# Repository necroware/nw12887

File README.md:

# Necroware's NW12887 RTC module

__ATTENTION:__ *this project was made for the SSOP-24 version of the RTC IC, if
you need the SO-24 version go for https://github.com/necroware/nwX287 project
instead*

This is a drop-in replacement for RTC modules with solid body. Such modules were
widely used on 486 and Pentium mainboards back in the days. After so many years
the battery inside of such modules got empty and there is no way to exchange it.
With empty battery BIOS settings can not be saved and so many mainboards can't
even boot properly. This alternative solution has a socket for CR1225 and the
battery can be easily replaced again, when it gets empty.

This part should be compatible with following RTC modules:

* Dallas DS1287 / DS12887 / DS12B887
* Benchmarq BQ3287
* ODIN OEC12C887

## Bill of Materials

Part | # | Description
-----|---|-------------------------------------
U1   | 1 | Real-Time Clock BQ3285LDSS SSOP-24
Y1   | 1 | Crystal oscillator 32.768kHz 6pF
BT1  | 1 | CR1220 / CR1225 SMD battery holder

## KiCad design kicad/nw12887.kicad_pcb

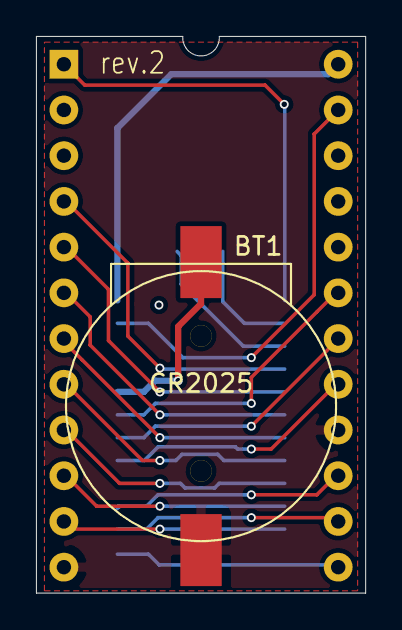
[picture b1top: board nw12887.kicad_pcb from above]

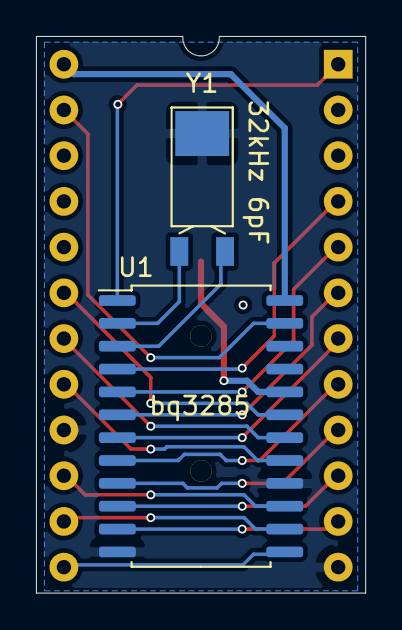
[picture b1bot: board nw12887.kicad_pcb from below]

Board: 2 copper layers, 18.3 x 30.9 mm, 4 parts (2 on the bottom side), 21 nets.

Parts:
BT1: CR2025; BatteryHolder_CR1220
U1: bq3285; SOIC-24W_7.5x15.4mm_P1.27mm
U2: ds12887; DIP-24_W15.24mm_Socket
Y1: 32kHz 6pF; Crystal_SMD_FrontierElectronics_FM206

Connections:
AD0: U1.4, U2.4
AD1: U1.5, U2.5
AD2: U1.6, U2.6
AD3: U1.7, U2.7
AD4: U1.8, U2.8
AD5: U1.9, U2.9
AD6: U1.10, U2.10
AD7: U1.11, U2.11
AS: U1.14, U2.14
BC: BT1.1, U1.20
CS: U1.13, U2.13
DS: U1.17, U2.17
GND: BT1.2, U1.12, U1.16, U2.12, U2.16, Y1.3
INT: U1.19, U2.19
MOT: U1.1, U2.1
RST: U1.18, U2.18
RW: U1.15, U2.15
SQW: U1.23, U2.23
VCC: U1.24, U2.24
X1: U1.2, Y1.2
X2: U1.3, Y1.1

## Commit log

2021-05-23 Replaced BQ3285 by bigger SO version
2021-06-04 Made SO-version
2021-06-04 Add readme, photos
2021-06-04 Add list of compatible modules
2021-06-04 Changed photo
2021-06-04 Add missing photo
2021-06-04 Now jpg photo
2021-06-04 Updated parts names
2021-06-04 Update PCB layout
2021-06-04 Add gerber to gitignore
2021-06-04 Silk layer changes, added lables
2021-06-16 Fixed battery socket position
